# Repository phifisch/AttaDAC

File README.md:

# AttaDAC
A simple 8-channel DAC for use with microcontroller boards (e.g. Arduino)

Inspired by the OctoDAC project, the aim of this PCB is to deliver analog-out with higher precision than is included on MCUs - when they have any real analog output at all. 
Having specifically a (biological) research setting in mind, this should help replace more sophisticated devices in applications requiring less precision. 
For instance, certain effectors such mass flow controllers have an intrinsic inertia, so we can get away with some fluctutation.
Measurements of this board's performance are still pending.

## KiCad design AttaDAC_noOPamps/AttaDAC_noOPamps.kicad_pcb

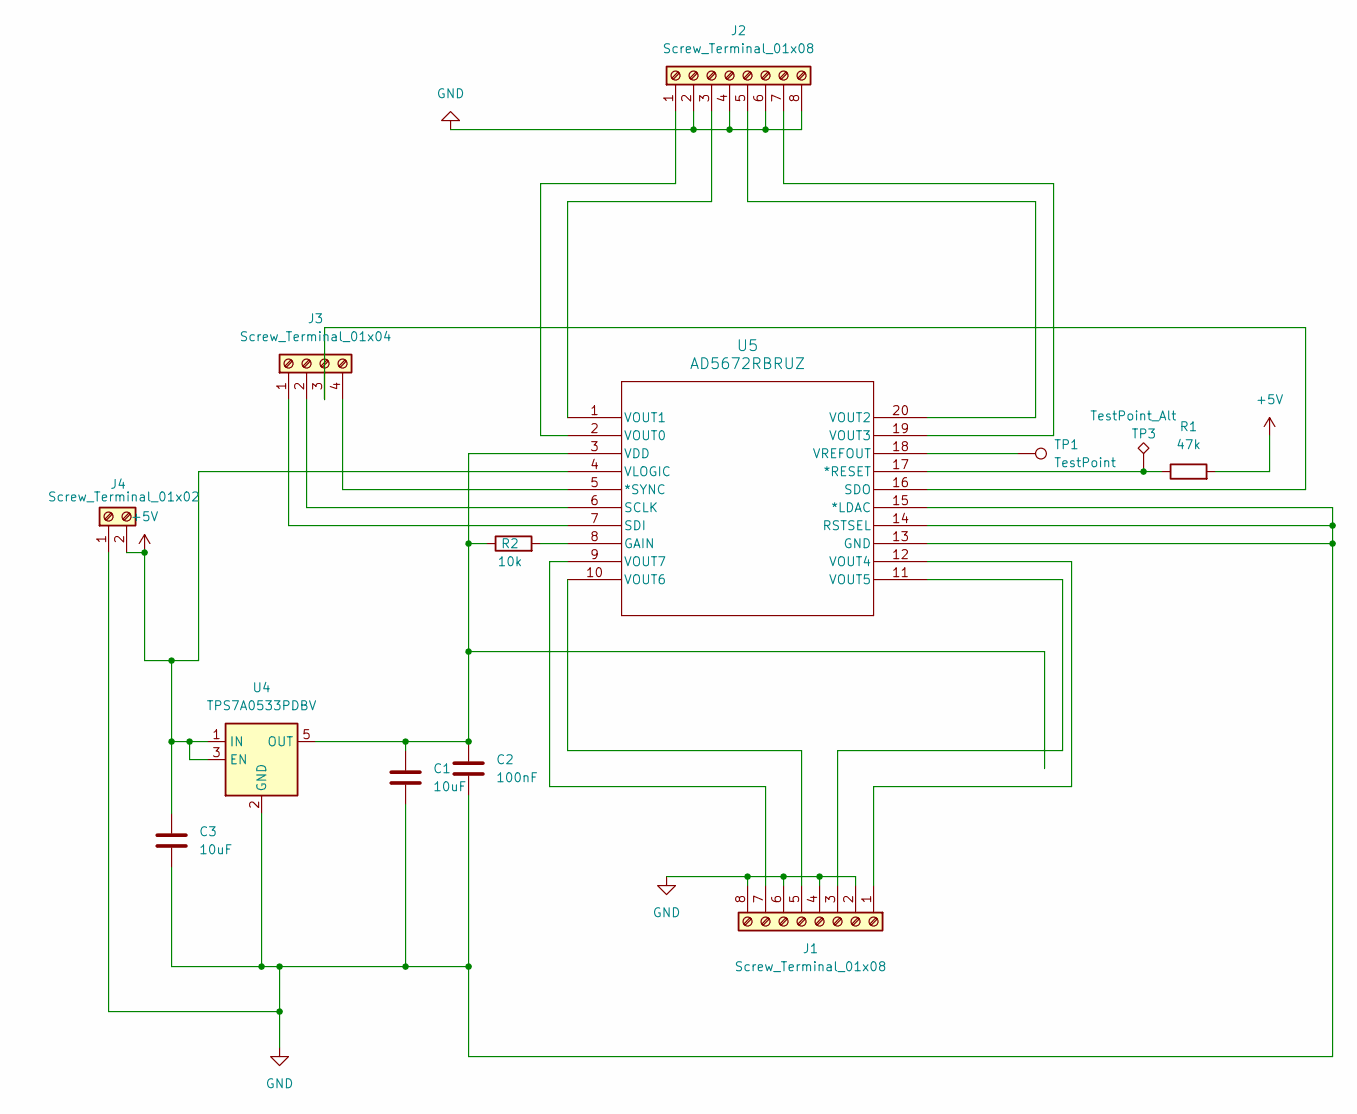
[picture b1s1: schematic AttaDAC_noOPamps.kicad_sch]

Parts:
C1: 10uF; C_Radial_D5.0mm_H7.0mm_P2.00mm
C2: 100nF; C_1210_3225Metric_Pad1.33x2.70mm_HandSolder
C3: 10uF; C_Radial_D8.0mm_H7.0mm_P3.50mm
J1, J2: Screw_Terminal_01x08; TerminalBlock_bornier-8_P5.08mm
J3: Screw_Terminal_01x04; TerminalBlock_bornier-4_P5.08mm
J4: Screw_Terminal_01x02; TerminalBlock_bornier-2_P5.08mm
R1: 47k; R_Axial_DIN0204_L3.6mm_D1.6mm_P5.08mm_Horizontal
R2: 10k; R_1206_3216Metric
TP1: TestPoint; TestPoint_Loop_D1.80mm_Drill1.0mm_Beaded
TP3: TestPoint_Alt; TestPoint_Loop_D1.80mm_Drill1.0mm_Beaded
U4: TPS7A0533PDBV; SOT-23-5
U5: AD5672RBRUZ; AD5672RBRUZ_ADI

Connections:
+5V: C3.1, J4.2, R1.2, U4.1 (IN), U4.3 (EN), U5.4 (VLOGIC)
GND: C1.2, C2.2, C3.2, J1.2, J1.4, J1.6, J1.8, J2.2, J2.4, J2.6, J2.8, J4.1, U4.2 (GND), U5.13 (GND), U5.14 (RSTSEL), U5.15 (*LDAC)
unnamed: J1.1, U5.12 (VOUT4)
unnamed: J1.3, U5.11 (VOUT5)
unnamed: J1.5, U5.10 (VOUT6)
unnamed: J1.7, U5.9 (VOUT7)
unnamed: J2.1, U5.2 (VOUT0)
unnamed: J2.3, U5.1 (VOUT1)
unnamed: J2.5, U5.20 (VOUT2)
unnamed: J2.7, U5.19 (VOUT3)
unnamed: J3.1, U5.7 (SDI)
unnamed: J3.2, U5.6 (SCLK)
unnamed: J3.3, U5.16 (SDO)
unnamed: J3.4, U5.5 (*SYNC)
unnamed: C1.1, C2.1, R2.1, U4.5 (OUT), U5.3 (VDD)
unnamed: R1.1, TP3.1, U5.17 (*RESET)
unnamed: R2.2, U5.8 (GAIN)
unnamed: TP1.1, U5.18 (VREFOUT)

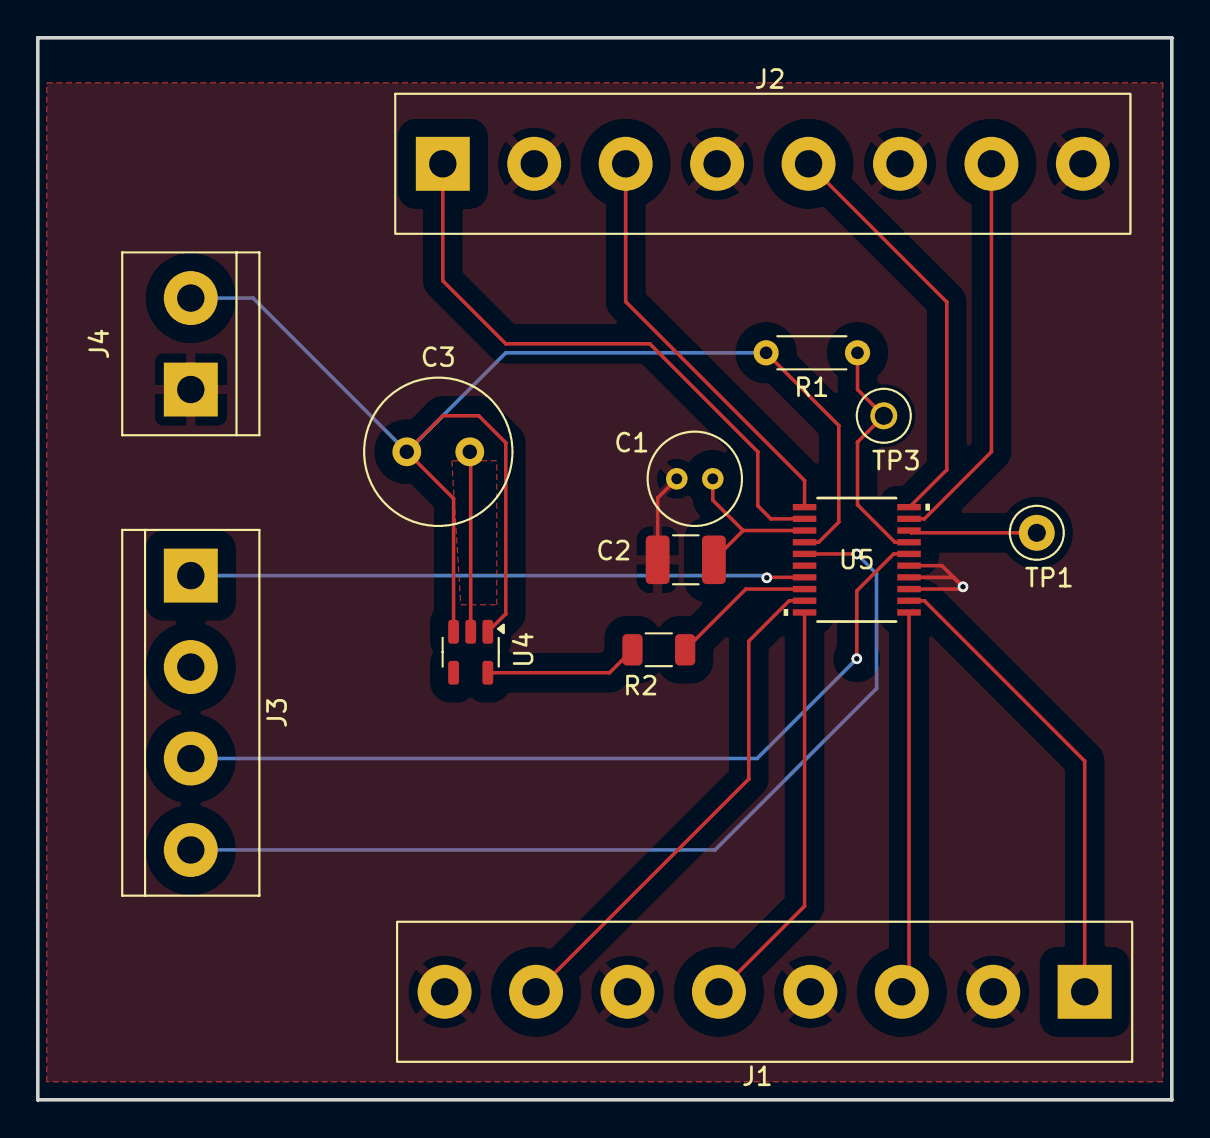
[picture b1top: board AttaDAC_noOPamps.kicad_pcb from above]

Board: 2 copper layers, 63.0 x 59.0 mm, 13 parts (0 on the bottom side), 18 nets.
